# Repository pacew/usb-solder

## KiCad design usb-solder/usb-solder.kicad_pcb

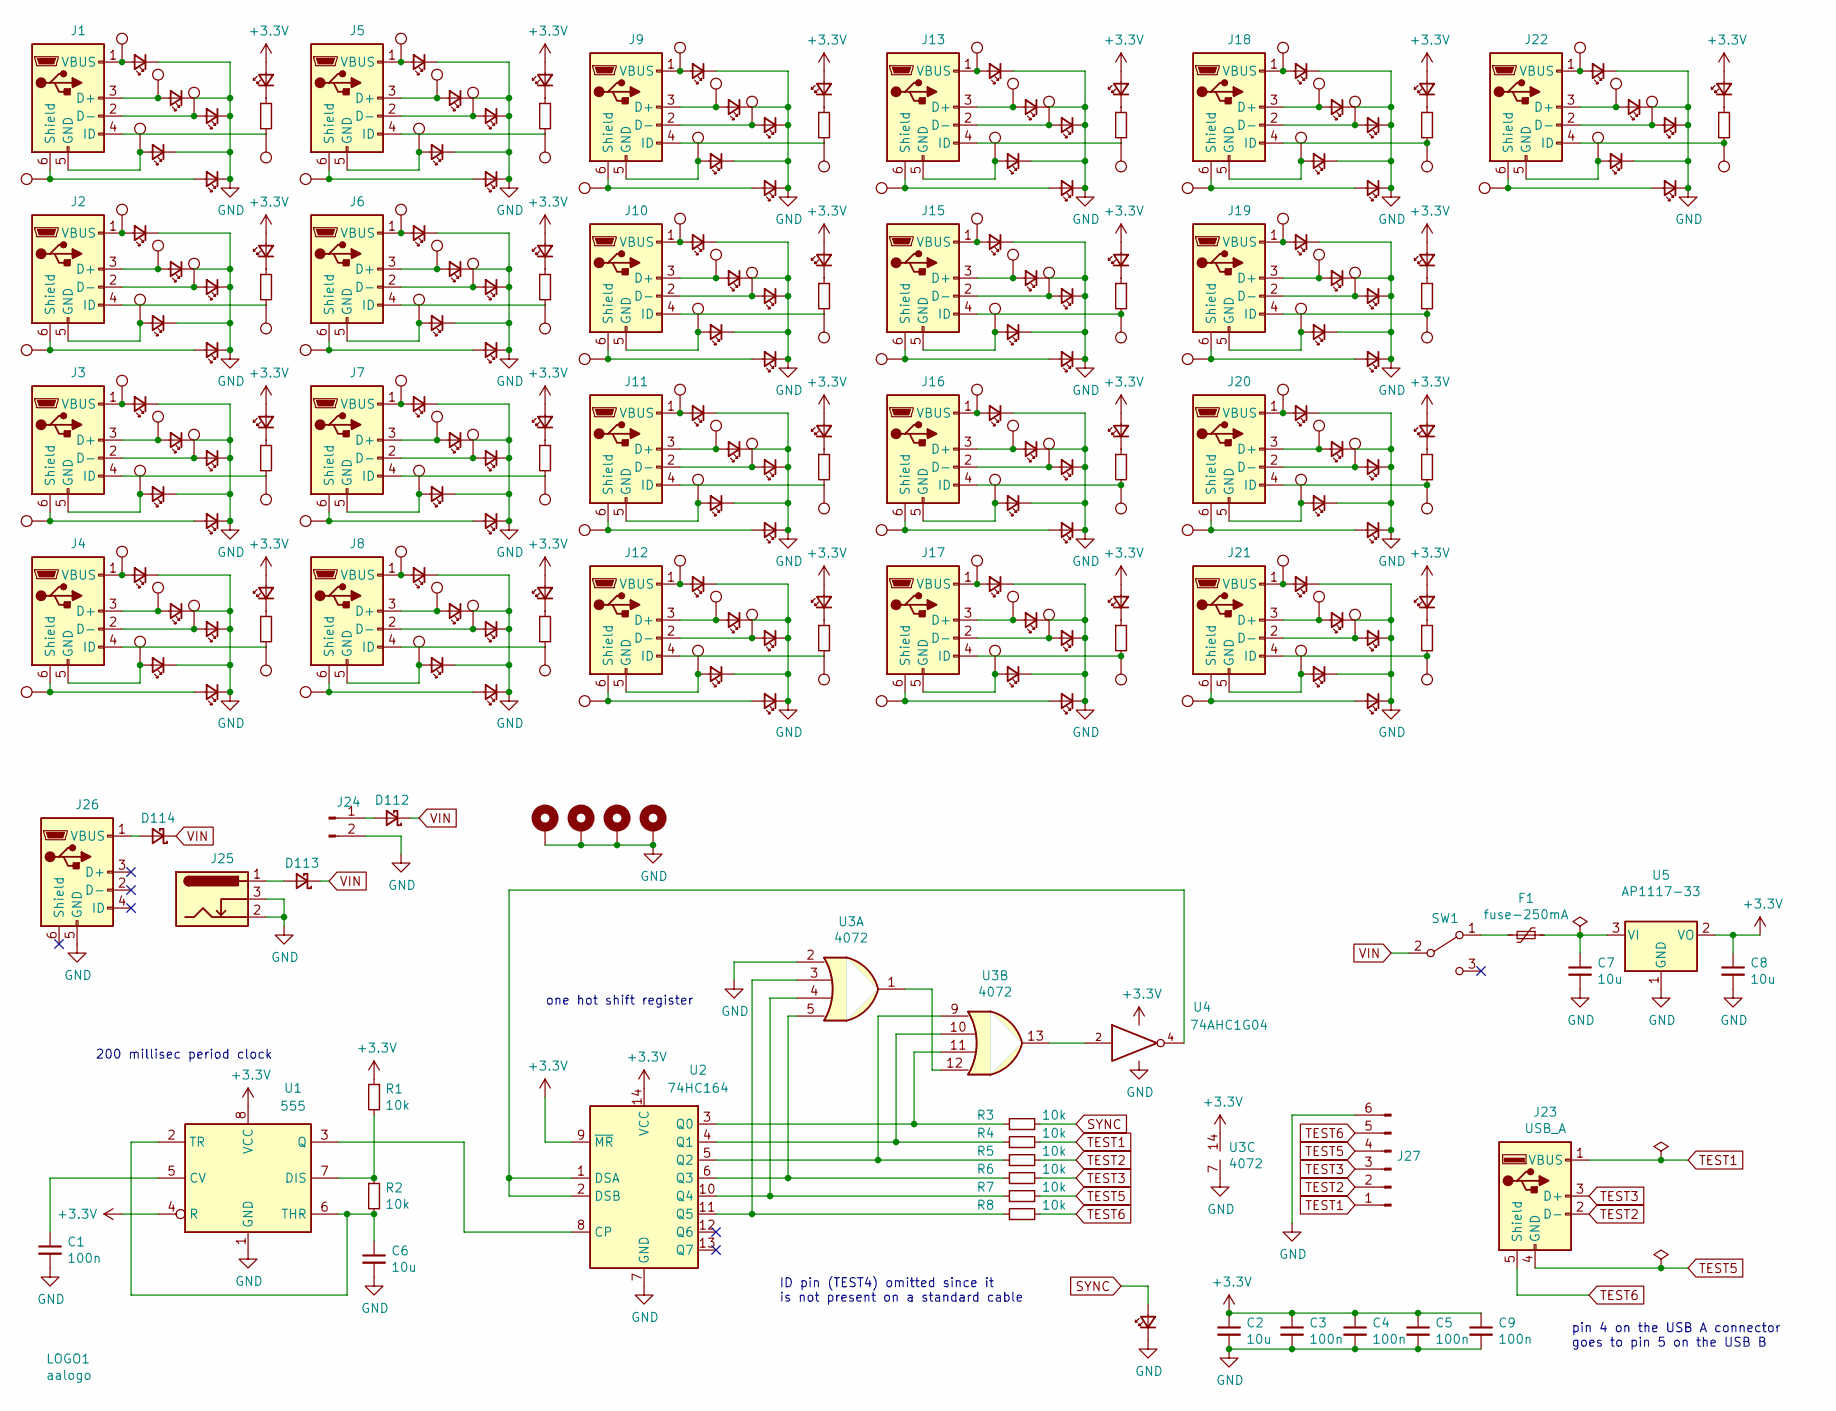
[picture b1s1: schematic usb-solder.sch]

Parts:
C1, C3, C4, C5, C9: 100n; C_0402_1005Metric; LCSC C1525
C2, C6, C7, C8: 10u; C_0402_1005Metric; LCSC C15525
D1, D2, D3, D4, D5, D6, D7, D8, D9, D10, D11, D12, D13, D14, D15, D16, D17, D18, D19, D20, D21, D22, D23, D24, D25, D26, D27, D28, D29, D30, D31, D32, D33, D34, D35, D36, D37, D38, D39, D40, D41, D42, D43, D44, D45, D46, D47, D48, D49, D50, D51, D52, D53, D54, D55, D56, D57, D58, D59, D60, D61, D63, D64, D65, D67, D68, D69, D71, D72, D73, D74, D77, D78, D79, D80, D81, D82, D83, D84, D85, D86, D87, D88, D89, D90, D91, D92, D93, D94, D95, D96, D97, D98, D99, D100, D101, D102, D103, D104, D105, D106, D107, D108, D109, D110, D111, D115, D116, D117, D118, D119, D120, D121, D122, D123, D124, D125, D126, D127, D128, D129, D130, D131, D132, D133, D135, D136: ledred; LED_0603_1608Metric; LCSC C2286
D112, D113, D114: SS210; D_SMA; LCSC C14996
F1: fuse-250mA; Fuse_1206_3216Metric; LCSC C70068
H1, H2, H3, H4: MountingHole_Pad; MountingHole_3.2mm_M3_Pad
J1, J2, J3, J4, J5, J6, J7, J8, J9, J10, J11, J12, J13, J15, J16, J17, J18, J19, J20, J21, J22, J26: USB_B_Micro; USB_Micro-B_Molex-105017-0001
J23: USB_A; USB_A_Stewart_SS-52100-001_Horizontal
J24: Conn_01x02_Male; PinHeader_1x02_P2.54mm_Vertical
J25: Barrel_Jack_Switch; BarrelJack_Horizontal
J27: Conn_01x06_Male; PinHeader_1x06_P2.54mm_Vertical
LOGO1: aalogo
R1, R2, R3, R4, R5, R6, R7, R8, R10, R11, R12, R13, R14, R15, R16, R17, R18, R19, R20, R21, R22, R23, R24, R25, R26, R27, R28, R30, R31: 10k; R_0402_1005Metric; LCSC C25744
SW1: SW_SPDT; Switch_Toggle_ATE1D-2M3-10-Z
TP1, TP2, TP3, TP4, TP5, TP6, TP7, TP8, TP9, TP10, TP11, TP12, TP13, TP14, TP15, TP16, TP17, TP18, TP19, TP20, TP21, TP22, TP23, TP24, TP25, TP26, TP27, TP28, TP29, TP30, TP31, TP32, TP33, TP34, TP35, TP36, TP37, TP38, TP39, TP40, TP41, TP42, TP43, TP44, TP45, TP46, TP47, TP48, TP49, TP50, TP51, TP52, TP53, TP54, TP55, TP56, TP57, TP58, TP59, TP60, TP61, TP62, TP63, TP64, TP65, TP66, TP67, TP68, TP69, TP70, TP71, TP72, TP73, TP75, TP76, TP77, TP78, TP81, TP82, TP83, TP84, TP85, TP87, TP88, TP89, TP91, TP92, TP93, TP95, TP96, TP97, TP98, TP99, TP100, TP101, TP102, TP103, TP104, TP105, TP106, TP107, TP108, TP109, TP110, TP111, TP112, TP113, TP114, TP115, TP116, TP117, TP118, TP119, TP120, TP121, TP122, TP123, TP124, TP125, TP126, TP127, TP128, TP129, TP130, TP131, TP132: TestPoint; TestPoint_Pad_D1.0mm
U1: 555; VSSOP-8_3.0x3.0mm_P0.65mm; LCSC C398924
U2: 74HC164; SOIC-14_3.9x8.7mm_P1.27mm; LCSC C6825
U3: 4072; SOIC-14_3.9x8.7mm_P1.27mm; LCSC C68527
U4: 74AHC1G04; SOT-353_SC-70-5; LCSC C7466
U5: AP1117-33; SOT-223-3_TabPin2; LCSC C6186

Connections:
+3V3: C2.1, C3.1, C4.1, C5.1, C8.1, C9.1, D115.2 (A), D116.2 (A), D117.2 (A), D118.2 (A), D119.2 (A), D120.2 (A), D121.2 (A), D122.2 (A), D123.2 (A), D124.2 (A), D125.2 (A), D126.2 (A), D127.2 (A), D128.2 (A), D129.2 (A), D130.2 (A), D131.2 (A), D132.2 (A), D133.2 (A), D135.2 (A), D136.2 (A), R1.1, U1.4 (R), U1.8 (VCC), U2.9 (~MR), U2.14 (VCC), U3.14, U4.5 (VCC), U5.2 (VO)
GND: C1.2, C2.2, C3.2, C4.2, C5.2, C6.2, C7.2, C8.2, C9.2, D1.1 (K), D2.1 (K), D3.1 (K), D4.1 (K), D5.1 (K), D6.1 (K), D7.1 (K), D8.1 (K), D9.1 (K), D10.1 (K), D11.1 (K), D12.1 (K), D13.1 (K), D14.1 (K), D15.1 (K), D16.1 (K), D17.1 (K), D18.1 (K), D19.1 (K), D20.1 (K), D21.1 (K), D22.1 (K), D23.1 (K), D24.1 (K), D25.1 (K), D26.1 (K), D27.1 (K), D28.1 (K), D29.1 (K), D30.1 (K), D31.1 (K), D32.1 (K), D33.1 (K), D34.1 (K), D35.1 (K), D36.1 (K), D37.1 (K), D38.1 (K), D39.1 (K), D40.1 (K), D41.1 (K), D42.1 (K), D43.1 (K), D44.1 (K), D45.1 (K), D46.1 (K), D47.1 (K), D48.1 (K), D49.1 (K), D50.1 (K), D51.1 (K), D52.1 (K), D53.1 (K), D54.1 (K), D55.1 (K), D56.1 (K), D57.1 (K), D58.1 (K), D59.1 (K), D60.1 (K), D61.1 (K), D63.1 (K), D64.1 (K), D65.1 (K), D67.1 (K), D68.1 (K), D69.1 (K), D71.1 (K), D72.1 (K), D73.1 (K), D74.1 (K), D77.1 (K), D78.1 (K), D79.1 (K), D80.1 (K), D81.1 (K), D82.1 (K), D83.1 (K), D84.1 (K), D85.1 (K), D86.1 (K), D87.1 (K), D88.1 (K), D89.1 (K), D90.1 (K), D91.1 (K), D92.1 (K), D93.1 (K), D94.1 (K), D95.1 (K), D96.1 (K), D97.1 (K), D98.1 (K), D99.1 (K), D100.1 (K), D101.1 (K), D102.1 (K), D103.1 (K), D104.1 (K), D105.1 (K), D106.1 (K), D107.1 (K), D108.1 (K), D109.1 (K), D110.1 (K), D111.1 (K), H1.1, H2.1, H3.1, H4.1, J24.2, J25.2, J25.3, J26.5 (GND), J27.6, U1.1 (GND), U2.7 (GND), U3.2, U3.7, U4.3 (GND), U5.1 (GND)
unnamed: C1.1, U1.5 (CV)
unnamed: C6.1, R2.2, U1.2 (TR), U1.6 (THR)
unnamed: C7.1, F1.1, U5.3 (VI)
unnamed: D1.2 (A), J1.1 (VBUS), TP5.1
unnamed: D2.2 (A), J2.1 (VBUS), TP7.1
unnamed: D3.2 (A), J3.1 (VBUS), TP9.1
unnamed: D4.2 (A), J4.1 (VBUS), TP11.1
unnamed: D5.2 (A), J1.5 (GND), TP13.1
unnamed: D6.2 (A), J2.5 (GND), TP14.1
unnamed: D7.2 (A), J3.5 (GND), TP15.1
unnamed: D8.2 (A), J4.5 (GND), TP16.1
unnamed: D9.2 (A), J1.3 (D+), TP17.1
unnamed: D10.2 (A), J2.3 (D+), TP18.1
unnamed: D11.2 (A), J3.3 (D+), TP19.1
unnamed: D12.2 (A), J4.3 (D+), TP20.1
unnamed: D13.2 (A), J1.2 (D-), TP21.1
unnamed: D14.2 (A), J1.6 (Shield), TP1.1
unnamed: D15.2 (A), J2.2 (D-), TP22.1
unnamed: D16.2 (A), J2.6 (Shield), TP2.1
unnamed: D17.2 (A), J3.2 (D-), TP23.1
unnamed: D18.2 (A), J3.6 (Shield), TP3.1
unnamed: D19.2 (A), J4.2 (D-), TP24.1
unnamed: D20.2 (A), J4.6 (Shield), TP4.1
unnamed: D21.2 (A), J5.1 (VBUS), TP29.1
unnamed: D22.2 (A), J6.1 (VBUS), TP31.1
unnamed: D23.2 (A), J7.1 (VBUS), TP33.1
unnamed: D24.2 (A), J8.1 (VBUS), TP35.1
unnamed: D25.2 (A), J5.5 (GND), TP37.1
unnamed: D26.2 (A), J6.5 (GND), TP38.1
unnamed: D27.2 (A), J7.5 (GND), TP39.1
unnamed: D28.2 (A), J8.5 (GND), TP40.1
unnamed: D29.2 (A), J5.3 (D+), TP41.1
unnamed: D30.2 (A), J6.3 (D+), TP42.1
unnamed: D31.2 (A), J7.3 (D+), TP43.1
unnamed: D32.2 (A), J8.3 (D+), TP44.1
unnamed: D33.2 (A), J5.2 (D-), TP45.1
unnamed: D34.2 (A), J5.6 (Shield), TP25.1
unnamed: D35.2 (A), J6.2 (D-), TP46.1
unnamed: D36.2 (A), J6.6 (Shield), TP26.1
unnamed: D37.2 (A), J7.2 (D-), TP47.1
unnamed: D38.2 (A), J7.6 (Shield), TP27.1
unnamed: D39.2 (A), J8.2 (D-), TP48.1
unnamed: D40.2 (A), J8.6 (Shield), TP28.1
unnamed: D41.2 (A), J9.1 (VBUS), TP53.1
unnamed: D42.2 (A), J10.1 (VBUS), TP55.1
unnamed: D43.2 (A), J11.1 (VBUS), TP57.1
unnamed: D44.2 (A), J12.1 (VBUS), TP59.1
unnamed: D45.2 (A), J9.5 (GND), TP61.1
unnamed: D46.2 (A), J10.5 (GND), TP62.1
unnamed: D47.2 (A), J11.5 (GND), TP63.1
unnamed: D48.2 (A), J12.5 (GND), TP64.1
unnamed: D49.2 (A), J9.3 (D+), TP65.1
unnamed: D50.2 (A), J10.3 (D+), TP66.1
unnamed: D51.2 (A), J11.3 (D+), TP67.1
unnamed: D52.2 (A), J12.3 (D+), TP68.1
unnamed: D53.2 (A), J9.2 (D-), TP69.1
unnamed: D54.2 (A), J9.6 (Shield), TP49.1
unnamed: D55.2 (A), J10.2 (D-), TP70.1
unnamed: D56.2 (A), J10.6 (Shield), TP50.1
unnamed: D57.2 (A), J11.2 (D-), TP71.1
unnamed: D58.2 (A), J11.6 (Shield), TP51.1
unnamed: D59.2 (A), J12.2 (D-), TP72.1
unnamed: D60.2 (A), J12.6 (Shield), TP52.1
unnamed: D61.2 (A), J13.1 (VBUS), TP77.1
unnamed: D63.2 (A), J15.1 (VBUS), TP81.1
unnamed: D64.2 (A), J16.1 (VBUS), TP83.1
unnamed: D65.2 (A), J13.5 (GND), TP85.1
unnamed: D67.2 (A), J15.5 (GND), TP87.1
unnamed: D68.2 (A), J16.5 (GND), TP88.1
unnamed: D69.2 (A), J13.3 (D+), TP89.1
unnamed: D71.2 (A), J15.3 (D+), TP91.1
unnamed: D72.2 (A), J16.3 (D+), TP92.1
unnamed: D73.2 (A), J13.2 (D-), TP93.1
unnamed: D74.2 (A), J13.6 (Shield), TP73.1
unnamed: D77.2 (A), J15.2 (D-), TP95.1
unnamed: D78.2 (A), J15.6 (Shield), TP75.1
unnamed: D79.2 (A), J16.2 (D-), TP96.1
unnamed: D80.2 (A), J16.6 (Shield), TP76.1
unnamed: D81.2 (A), J17.1 (VBUS), TP101.1
unnamed: D82.2 (A), J18.1 (VBUS), TP103.1
unnamed: D83.2 (A), J19.1 (VBUS), TP105.1
unnamed: D84.2 (A), J20.1 (VBUS), TP107.1
unnamed: D85.2 (A), J17.5 (GND), TP109.1
unnamed: D86.2 (A), J18.5 (GND), TP110.1
unnamed: D87.2 (A), J19.5 (GND), TP111.1
unnamed: D88.2 (A), J20.5 (GND), TP112.1
unnamed: D89.2 (A), J17.3 (D+), TP113.1
unnamed: D90.2 (A), J18.3 (D+), TP114.1
unnamed: D91.2 (A), J19.3 (D+), TP115.1
unnamed: D92.2 (A), J20.3 (D+), TP116.1
unnamed: D93.2 (A), J17.2 (D-), TP117.1
unnamed: D94.2 (A), J17.6 (Shield), TP97.1
unnamed: D95.2 (A), J18.2 (D-), TP118.1
unnamed: D96.2 (A), J18.6 (Shield), TP98.1
unnamed: D97.2 (A), J19.2 (D-), TP119.1
unnamed: D98.2 (A), J19.6 (Shield), TP99.1
unnamed: D99.2 (A), J20.2 (D-), TP120.1
unnamed: D100.2 (A), J20.6 (Shield), TP100.1
unnamed: D101.2 (A), J21.1 (VBUS), TP123.1
unnamed: D102.2 (A), J22.1 (VBUS), TP125.1
unnamed: D103.2 (A), J21.5 (GND), TP127.1
unnamed: D104.2 (A), J22.5 (GND), TP128.1
unnamed: D105.2 (A), J21.3 (D+), TP129.1
unnamed: D106.2 (A), J22.3 (D+), TP130.1
unnamed: D107.2 (A), J21.2 (D-), TP131.1
unnamed: D108.2 (A), J21.6 (Shield), TP121.1
unnamed: D109.2 (A), J22.2 (D-), TP132.1
unnamed: D110.2 (A), J22.6 (Shield), TP122.1
unnamed: D112.2 (A), J24.1
unnamed: D113.2 (A), J25.1
unnamed: D114.2 (A), J26.1 (VBUS)
unnamed: D115.1 (K), R10.1
unnamed: D116.1 (K), R11.1
unnamed: D117.1 (K), R12.1
unnamed: D118.1 (K), R13.1
unnamed: D119.1 (K), R14.1
unnamed: D120.1 (K), R15.1
unnamed: D121.1 (K), R16.1
unnamed: D122.1 (K), R17.1
unnamed: D123.1 (K), R18.1
unnamed: D124.1 (K), R19.1
unnamed: D125.1 (K), R20.1
unnamed: D126.1 (K), R21.1
unnamed: D127.1 (K), R22.1
unnamed: D128.1 (K), R23.1
unnamed: D129.1 (K), R24.1
unnamed: D130.1 (K), R25.1
unnamed: D131.1 (K), R26.1
unnamed: D132.1 (K), R27.1
unnamed: D133.1 (K), R28.1
unnamed: D135.1 (K), R30.1
unnamed: D136.1 (K), R31.1
unnamed: F1.2, SW1.1 (A)
unnamed: J1.4 (ID), R16.2, TP6.1
unnamed: J2.4 (ID), R17.2, TP8.1
unnamed: J3.4 (ID), R18.2, TP10.1
unnamed: J4.4 (ID), R19.2, TP12.1
unnamed: J5.4 (ID), R20.2, TP30.1
unnamed: J6.4 (ID), R21.2, TP32.1
unnamed: J7.4 (ID), R22.2, TP34.1
unnamed: J8.4 (ID), R23.2, TP36.1
unnamed: J9.4 (ID), R24.2, TP54.1
unnamed: J10.4 (ID), R25.2, TP56.1
unnamed: J11.4 (ID), R26.2, TP58.1
unnamed: J12.4 (ID), R27.2, TP60.1
unnamed: J13.4 (ID), R28.2, TP78.1
unnamed: J15.4 (ID), R30.2, TP82.1
unnamed: J16.4 (ID), R31.2, TP84.1
unnamed: J17.4 (ID), R11.2, TP102.1
unnamed: J18.4 (ID), R12.2, TP104.1
unnamed: J19.4 (ID), R13.2, TP106.1
unnamed: J20.4 (ID), R14.2, TP108.1
unnamed: J21.4 (ID), R10.2, TP124.1
unnamed: J22.4 (ID), R15.2, TP126.1
unnamed: R1.2, R2.1, U1.7 (DIS)
unnamed: R3.1, U2.3 (Q0), U3.11
unnamed: R4.1, U2.4 (Q1), U3.10
unnamed: R5.1, U2.5 (Q2), U3.9
unnamed: R6.1, U2.6 (Q3), U3.5
unnamed: R7.1, U2.10 (Q4), U3.4
unnamed: R8.1, U2.11 (Q5), U3.3
unnamed: U1.3 (Q), U2.8 (CP)
unnamed: U2.1 (DSA), U2.2 (DSB), U4.4
unnamed: U3.1, U3.12
unnamed: U3.13, U4.2
SYNC: D111.2 (A), R3.2
TEST1: J23.1 (VBUS), J27.1, R4.2
TEST2: J23.2 (D-), J27.2, R5.2
TEST3: J23.3 (D+), J27.3, R6.2
TEST5: J23.4 (GND), J27.4, R7.2
TEST6: J23.5 (Shield), J27.5, R8.2
VIN: D112.1 (K), D113.1 (K), D114.1 (K), SW1.2 (B)

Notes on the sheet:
one hot shift register
pin 4 on the USB A connector goes to pin 5 on the USB B
ID pin (TEST4) omitted since it is not present on a standard cable
200 millisec period clock

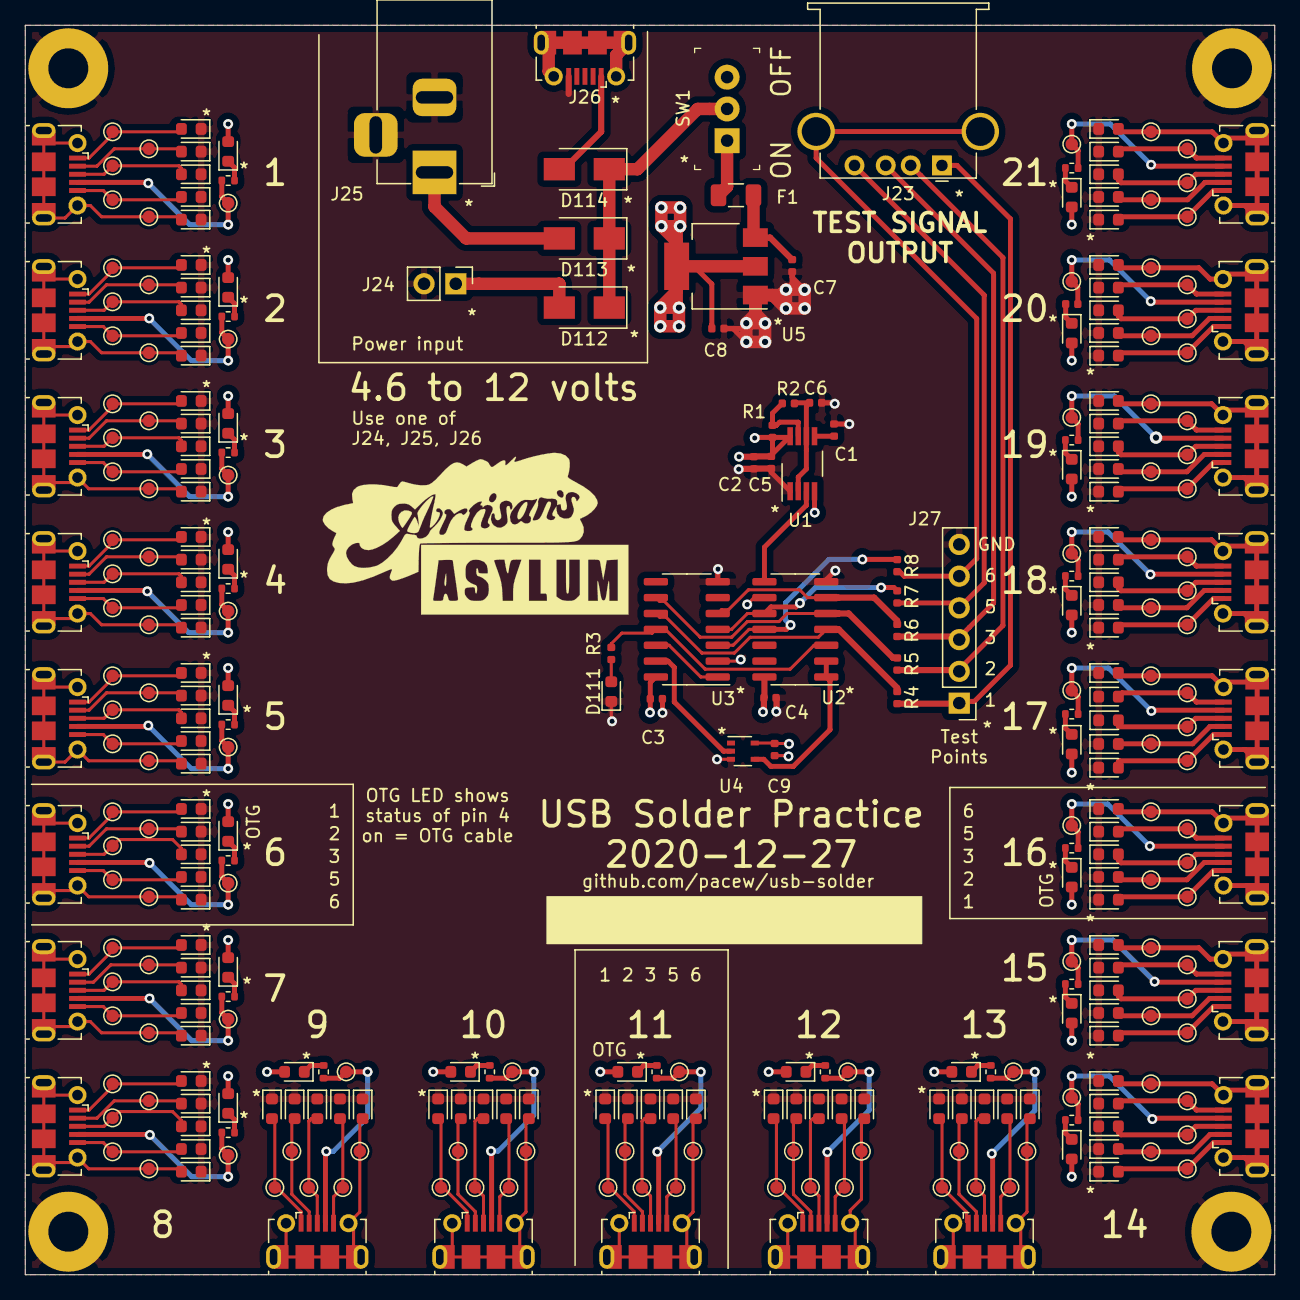
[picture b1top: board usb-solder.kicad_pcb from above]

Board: 4 copper layers, 100.0 x 100.0 mm, 332 parts (0 on the bottom side), 174 nets.

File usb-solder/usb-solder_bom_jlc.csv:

"Comment","Designator","Footprint","LCSC Part #"
"100n","C3,C4,C1,C5,C9","C_0402_1005Metric","C1525"
"10u","C6,C2,C8,C7","C_0402_1005Metric","C15525"
"ledred","D1,D9,D13,D5,D14,D2,D10,D15,D6,D16,D3,D11,D17,D7,D18,D4,D12,D19,D8,D20,D21,D29,D33,D25,D34,D22,D30,D35,D26,D36,D23,D31,D37,D27,D38,D24,D32,D39,D28,D40,D41,D49,D53,D45,D54,D42,D50,D55,D46,D56,D43,D51,D57,D47,D58,D44,D52,D59,D48,D60,D61,D69,D73,D65,D74,D63,D71,D77,D67,D78,D64,D72,D79,D68,D80,D81,D89,D93,D85,D94,D82,D90,D95,D86,D96,D83,D91,D97,D87,D98,D84,D92,D99,D88,D100,D101,D105,D107,D103,D108,D102,D106,D109,D104,D110,D111,D115,D120,D116,D117,D118,D119,D133,D135,D136,D132,D131,D130,D129,D125,D126,D127,D128,D124,D123,D122,D121","LED_0603_1608Metric","C2286"
"SS210","D113,D112,D114","D_SMA","C14996"
"fuse-250mA","F1","Fuse_1206_3216Metric","C70068"
"10k","R2,R1,R3,R4,R5,R6,R7,R8,R10,R15,R11,R12,R13,R14,R28,R30,R31,R27,R26,R25,R24,R20,R21,R22,R23,R19,R18,R17,R16","R_0402_1005Metric","C25744"
"555","U1","VSSOP-8_3.0x3.0mm_P0.65mm","C398924"
"74HC164","U2","SOIC-14_3.9x8.7mm_P1.27mm","C6825"
"4072","U3","SOIC-14_3.9x8.7mm_P1.27mm","C68527"
"74AHC1G04","U4","SOT-353_SC-70-5","C7466"
"AP1117-33","U5","SOT-223-3_TabPin2","C6186"

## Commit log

2020-12-24 start
2020-12-24 routing
2020-12-25 check
2020-12-26 script
2020-12-26 parts
2020-12-26 filter
2020-12-27 cleanup
2020-12-27 silk
2020-12-27 logo
2020-12-28 image
